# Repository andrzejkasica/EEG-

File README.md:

# EEG-
EEG hardware project. Device based on STM32

**Hardware**
 - STM32F446RE
 - BLE module
 - USB Type-C connector + USB Isolator
 - AFE:
   ADS1299 (TI) 8 chan
   ADS1298 (TI) 8 chan
   AD7771 (Analog Devices) 8 chan
   INA114 - single channel
 - LDO
 - Electrodes (to be chosen)
 - Electrode cables
 - Battery / Acu 

**Software & Tools**
  - STM32CubeIDE
  - eDesignSuite - ST's online design tools: st.com/edesign
  - MNE-Python
  - BESA Simulator
  - Python

**Electrodes**
- Wet (Ag/AgCl)	Best signal quality, low impedance	Requires gel, preparation time
- Dry	No prep, comfortable	Higher impedance, more noise
- Semi-dry	Balance of both	Limited availability

**Reference Open source projects**
  - https://pieeg.com/microbci/
    STM32 shield for EEG/EMG/ECG,
    8 channels, NUCLEO-WB55 compatible, Python software
  - https://github.com/pieeg-club/ironbci
    Wearable BCI with ADS1299 + STM32 
    BLE, mobile SDK, 3D printable headset designs
  - https://www.crowdsupply.com/neuroidss/freeeeg32
    32-channel research-grade EEG
    STM32H7, 4x AD7771 ADCs, high-quality acquisition
  - https://www.hackster.io/mustafamelihcan/open-source-diy-eeg-brainwaves-on-a-custom-pcb-99146e
    Single-channel custom PCB EEG

**Diagram**
┌─────────────┐    ┌──────────────┐    ┌─────────────┐    ┌──────────────┐
│  Electrodes │───▶│  AFE         │───▶│  STM32 MCU  │───▶│  Output      │
│  (Scalp)    │    │  (ADS1299)   │    │  (F4/H7)    │    │  (USB/BLE)   │
└─────────────┘    └──────────────┘    └─────────────┘    └──────────────┘
                         │                    │
                   ┌─────┴─────┐        ┌─────┴─────┐
                   │ SPI Bus   │        │ DSP/Filter│
                   │ (16 MHz)  │        │ Processing│
                   └───────────┘        └───────────┘

**Links**
https://www.ti.com/product/ADS1299
https://www.ti.com/lit/an/sbaa188a/sbaa188a.pdf
https://www.st.com/content/st_com/en/support/learning/stm32-education.html
https://www.instructables.com/Measure-EEG-With-STM32-Nucleo-Board/

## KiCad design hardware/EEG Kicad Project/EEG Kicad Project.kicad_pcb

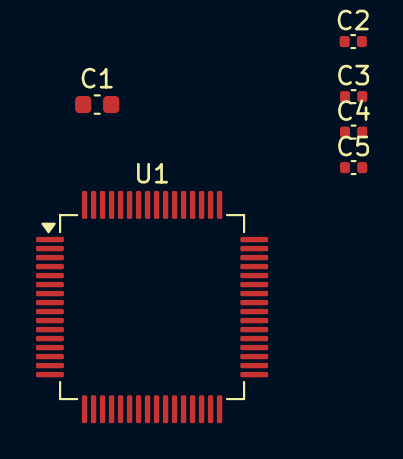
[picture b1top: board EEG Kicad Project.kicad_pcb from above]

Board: 2 copper layers, 6 parts (0 on the bottom side), 2 nets, no tracks yet.

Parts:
C1: 1u; C_0603_1608Metric
C2, C3, C4, C5: 100n; C_0402_1005Metric
U1: STM32F446RETx; LQFP-64_10x10mm_P0.5mm

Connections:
+3V3: C1.1, C2.1, C3.1, C4.1, C5.1, U1.19 (VDD), U1.32 (VDD), U1.48 (VDD), U1.64 (VDD)
GND: C1.2, C2.2, C3.2, C4.2, C5.2, U1.18 (VSS), U1.31 (VSS), U1.47 (VSS), U1.63 (VSS)

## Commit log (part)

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2026-01-05 Update README with project details and references
    Added hardware specifications, software tools, and references for the EEG project.
2026-01-05 Revise references and include system diagram
    Updated project references and added a diagram.
2026-01-05 Format project references in README
    Updated references to open source projects in README.
2026-01-05 Enhance README with AFE details and additional resources
    Added detailed information about AFE components, software tools, electrodes, and relevant links.
2026-01-05 Update hardware components and software tools in README
2026-04-20 structure init, add ignore filer for firmware
2026-05-04 add eclipse gitignore file
2026-05-04 added stm32IDE files to gitignore for hardware
2026-06-22 First sketch of STM32 configuration, adding ioc file
2026-06-22 add references.md file with git repos and help articles
2026-06-24 add Kicad porject with gitignore
2026-06-24 Added uC and started organizing schematic into sections: Power, uC, Analog
2026-06-27 Added datasheet, modify STM32 pinout in MX, added labels on schematic, added STM32 hierarch sheet
2026-06-27 Deleted folders: EEG kicad Project, PCB, Schematic
2026-06-27 Add '-auto' to .gitignore
2026-06-27 added */#autosaved_files# to gitignore
2026-06-27 rename spaces from Catalogs and files
2026-06-28 Added ADS1299, hierarchical sheets for: power, usb, analog, stm
2026-06-29 Readme change, add -5V, some organizational changes
